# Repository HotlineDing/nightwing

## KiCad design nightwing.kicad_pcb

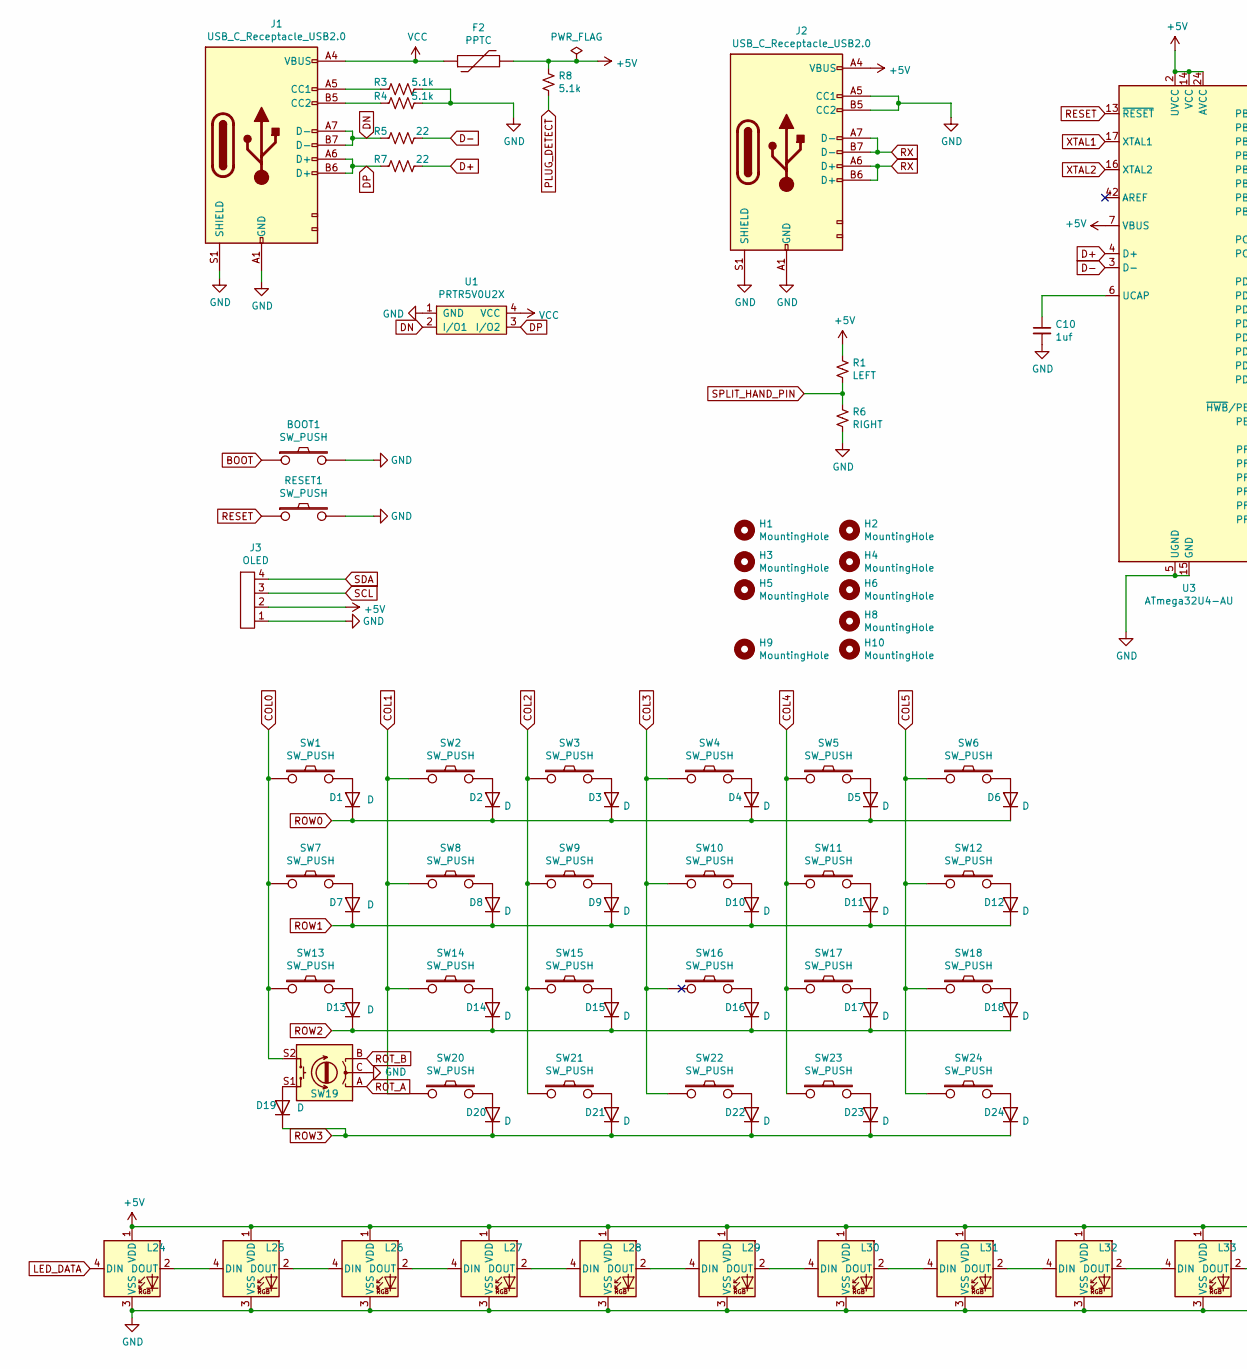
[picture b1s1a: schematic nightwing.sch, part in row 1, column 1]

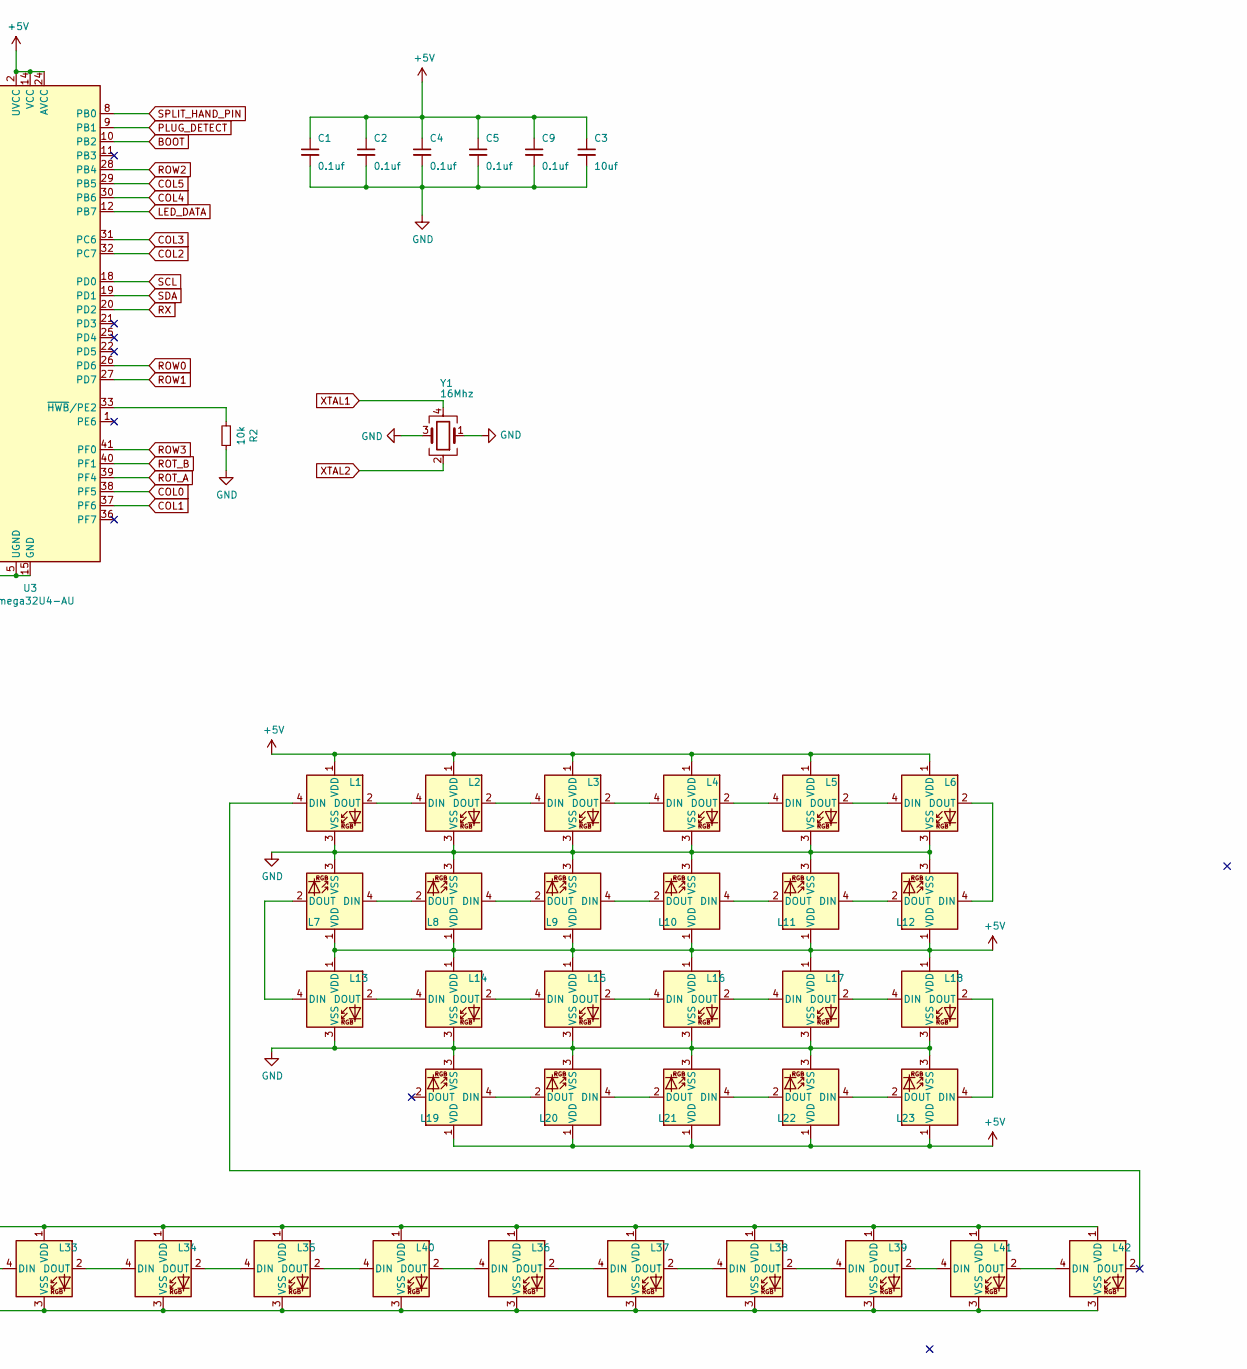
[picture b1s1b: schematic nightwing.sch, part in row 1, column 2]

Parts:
BOOT1: SW_PUSH; SW_Push_1P1T_NO_6x6mm_H9.5mm
C1, C2, C4, C5, C9: 0.1uf; C_0805_2012Metric
C3: 10uf; C_0805_2012Metric
C10: 1uf; C_0805_2012Metric
D1, D2, D3, D4, D5, D6, D7, D8, D9, D10, D11, D12, D13, D14, D15, D16, D17, D18, D19, D20, D21, D22, D23, D24: D; D_SOD-123
F2: PPTC; Fuse_1206_3216Metric
H1, H2, H3, H4, H5, H6, H8, H9, H10: MountingHole; MountingHole_2.2mm_M2_DIN965
J1, J2: USB_C_Receptacle_USB2.0; USB_C_Receptacle_HRO_TYPE-C-31-M-12
J3: OLED; OLED-SSD1306-128x64
L1, L2, L3, L4, L5, L6, L7, L8, L9, L10, L11, L12, L13, L14, L15, L16, L17, L18, L19, L20, L21, L22, L23: SK2812Mini-E; SK6812Mini-E
L24, L25, L26, L27, L28, L29, L30, L31, L32, L33, L34, L35, L36, L37, L38, L39, L40, L41, L42: WS2812B; ws2812_reversible
R1: LEFT; R_0805_2012Metric
R2: 10k; R_0805_2012Metric
R3, R4, R8: 5.1k; R_0805_2012Metric
R5, R7: 22; R_0805_2012Metric
R6: RIGHT; R_0805_2012Metric
RESET1: SW_PUSH; SW_Push_1P1T_NO_6x6mm_H9.5mm
SW1, SW2, SW3, SW4, SW5, SW6, SW7, SW8, SW9, SW10, SW11, SW12, SW13, SW14, SW15, SW16, SW17, SW18, SW20, SW21, SW22, SW23, SW24: SW_PUSH; MX-1U-Hotswap
SW19: Rotary_Encoder; RotaryEncoder_EC11
U1: PRTR5V0U2X; SOT-143_Handsoldering
U3: ATmega32U4-AU; TQFP-44_10x10mm_P0.8mm
Y1: 16Mhz; Crystal_SMD_3225-4Pin_3.2x2.5mm

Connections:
+5V: C1.1, C2.1, C3.1, C4.1, C5.1, C9.1, F2.2, J2.A4 (VBUS), J2.B4 (VBUS), J3.2, L1.1 (VDD), L2.1 (VDD), L3.1 (VDD), L4.1 (VDD), L5.1 (VDD), L6.1 (VDD), L7.1 (VDD), L8.1 (VDD), L9.1 (VDD), L10.1 (VDD), L11.1 (VDD), L12.1 (VDD), L13.1 (VDD), L14.1 (VDD), L15.1 (VDD), L16.1 (VDD), L17.1 (VDD), L18.1 (VDD), L19.1 (VDD), L20.1 (VDD), L21.1 (VDD), L22.1 (VDD), L23.1 (VDD), L24.1 (VDD), L25.1 (VDD), L26.1 (VDD), L27.1 (VDD), L28.1 (VDD), L29.1 (VDD), L30.1 (VDD), L31.1 (VDD), L32.1 (VDD), L33.1 (VDD), L34.1 (VDD), L35.1 (VDD), L36.1 (VDD), L37.1 (VDD), L38.1 (VDD), L39.1 (VDD), L40.1 (VDD), L41.1 (VDD), L42.1 (VDD), R1.1, R8.1, U3.2 (UVCC), U3.7 (VBUS), U3.14 (VCC), U3.24 (AVCC), U3.34 (VCC), U3.44 (AVCC)
BOOT: BOOT1.1, U3.10 (PB2)
COL0: SW1.1, SW7.1, SW13.1, SW19.S2, U3.38 (PF5)
COL1: SW2.1, SW8.1, SW14.1, SW20.1, U3.37 (PF6)
COL2: SW3.1, SW9.1, SW15.1, SW21.1, U3.32 (PC7)
COL3: SW4.1, SW10.1, SW16.1, SW22.1, U3.31 (PC6)
COL4: SW5.1, SW11.1, SW17.1, SW23.1, U3.30 (PB6)
COL5: SW6.1, SW12.1, SW18.1, SW24.1, U3.29 (PB5)
D+: R7.1, U3.4 (D+)
D-: R5.1, U3.3 (D-)
DN: J1.A7 (D-), J1.B7 (D-), R5.2, U1.2 (I/O1)
DP: J1.A6 (D+), J1.B6 (D+), R7.2, U1.3 (I/O2)
GND: BOOT1.2, C1.2, C2.2, C3.2, C4.2, C5.2, C9.2, C10.2, J1.A1 (GND), J1.B1 (GND), J1.S1 (SHIELD), J2.A1 (GND), J2.A5 (CC1), J2.B1 (GND), J2.B5 (CC2), J2.S1 (SHIELD), J3.1, L1.3 (VSS), L2.3 (VSS), L3.3 (VSS), L4.3 (VSS), L5.3 (VSS), L6.3 (VSS), L7.3 (VSS), L8.3 (VSS), L9.3 (VSS), L10.3 (VSS), L11.3 (VSS), L12.3 (VSS), L13.3 (VSS), L14.3 (VSS), L15.3 (VSS), L16.3 (VSS), L17.3 (VSS), L18.3 (VSS), L19.3 (VSS), L20.3 (VSS), L21.3 (VSS), L22.3 (VSS), L23.3 (VSS), L24.3 (VSS), L25.3 (VSS), L26.3 (VSS), L27.3 (VSS), L28.3 (VSS), L29.3 (VSS), L30.3 (VSS), L31.3 (VSS), L32.3 (VSS), L33.3 (VSS), L34.3 (VSS), L35.3 (VSS), L36.3 (VSS), L37.3 (VSS), L38.3 (VSS), L39.3 (VSS), L40.3 (VSS), L41.3 (VSS), L42.3 (VSS), R2.1, R3.1, R4.1, R6.2, RESET1.2, SW19.C, U1.1 (GND), U3.5 (UGND), U3.15 (GND), U3.23 (GND), U3.35 (GND), U3.43 (GND), Y1.1, Y1.3
LED_DATA: L24.4 (DIN), U3.12 (PB7)
unnamed: C10.1, U3.6 (UCAP)
unnamed: D1.2 (A), SW1.2
unnamed: D2.2 (A), SW2.2
unnamed: D3.2 (A), SW3.2
unnamed: D4.2 (A), SW4.2
unnamed: D5.2 (A), SW5.2
unnamed: D6.2 (A), SW6.2
unnamed: D7.2 (A), SW7.2
unnamed: D8.2 (A), SW8.2
unnamed: D9.2 (A), SW9.2
unnamed: D10.2 (A), SW10.2
unnamed: D11.2 (A), SW11.2
unnamed: D12.2 (A), SW12.2
unnamed: D13.2 (A), SW13.2
unnamed: D14.2 (A), SW14.2
unnamed: D15.2 (A), SW15.2
unnamed: D16.2 (A), SW16.2
unnamed: D17.2 (A), SW17.2
unnamed: D18.2 (A), SW18.2
unnamed: D19.2 (A), SW19.S1
unnamed: D20.2 (A), SW20.2
unnamed: D21.2 (A), SW21.2
unnamed: D22.2 (A), SW22.2
unnamed: D23.2 (A), SW23.2
unnamed: D24.2 (A), SW24.2
unnamed: J1.A5 (CC1), R3.2
unnamed: J1.B5 (CC2), R4.2
unnamed: L1.2 (DOUT), L2.4 (DIN)
unnamed: L1.4 (DIN), L42.2 (DOUT)
unnamed: L2.2 (DOUT), L3.4 (DIN)
unnamed: L3.2 (DOUT), L4.4 (DIN)
unnamed: L4.2 (DOUT), L5.4 (DIN)
unnamed: L5.2 (DOUT), L6.4 (DIN)
unnamed: L7.4 (DIN), L8.2 (DOUT)
unnamed: L8.4 (DIN), L9.2 (DOUT)
unnamed: L9.4 (DIN), L10.2 (DOUT)
unnamed: L10.4 (DIN), L11.2 (DOUT)
unnamed: L11.4 (DIN), L12.2 (DOUT)
unnamed: L6.2 (DOUT), L12.4 (DIN)
unnamed: L13.2 (DOUT), L14.4 (DIN)
unnamed: L7.2 (DOUT), L13.4 (DIN)
unnamed: L14.2 (DOUT), L15.4 (DIN)
unnamed: L15.2 (DOUT), L16.4 (DIN)
unnamed: L16.2 (DOUT), L17.4 (DIN)
unnamed: L17.2 (DOUT), L18.4 (DIN)
unnamed: L18.2 (DOUT), L23.4 (DIN)
unnamed: L19.4 (DIN), L20.2 (DOUT)
unnamed: L20.4 (DIN), L21.2 (DOUT)
unnamed: L21.4 (DIN), L22.2 (DOUT)
unnamed: L22.4 (DIN), L23.2 (DOUT)
unnamed: L24.2 (DOUT), L25.4 (DIN)
unnamed: L25.2 (DOUT), L26.4 (DIN)
unnamed: L26.2 (DOUT), L27.4 (DIN)
unnamed: L27.2 (DOUT), L28.4 (DIN)
unnamed: L28.2 (DOUT), L29.4 (DIN)
unnamed: L29.2 (DOUT), L30.4 (DIN)
unnamed: L30.2 (DOUT), L31.4 (DIN)
unnamed: L31.2 (DOUT), L32.4 (DIN)
unnamed: L32.2 (DOUT), L33.4 (DIN)
unnamed: L33.2 (DOUT), L34.4 (DIN)
unnamed: L34.2 (DOUT), L35.4 (DIN)
unnamed: L35.2 (DOUT), L40.4 (DIN)
unnamed: L36.2 (DOUT), L37.4 (DIN)
unnamed: L36.4 (DIN), L40.2 (DOUT)
unnamed: L37.2 (DOUT), L38.4 (DIN)
unnamed: L38.2 (DOUT), L39.4 (DIN)
unnamed: L39.2 (DOUT), L41.4 (DIN)
unnamed: L41.2 (DOUT), L42.4 (DIN)
unnamed: R2.2, U3.33 (~HWB~/PE2)
PLUG_DETECT: R8.2, U3.9 (PB1)
RESET: RESET1.1, U3.13 (~RESET)
ROT_A: SW19.A, U3.39 (PF4)
ROT_B: SW19.B, U3.40 (PF1)
ROW0: D1.1 (K), D2.1 (K), D3.1 (K), D4.1 (K), D5.1 (K), D6.1 (K), U3.26 (PD6)
ROW1: D7.1 (K), D8.1 (K), D9.1 (K), D10.1 (K), D11.1 (K), D12.1 (K), U3.27 (PD7)
ROW2: D13.1 (K), D14.1 (K), D15.1 (K), D16.1 (K), D17.1 (K), D18.1 (K), U3.28 (PB4)
ROW3: D19.1 (K), D20.1 (K), D21.1 (K), D22.1 (K), D23.1 (K), D24.1 (K), U3.41 (PF0)
RX: J2.A6 (D+), J2.A7 (D-), J2.B6 (D+), J2.B7 (D-), U3.20 (PD2)
SCL: J3.3, U3.18 (PD0)
SDA: J3.4, U3.19 (PD1)
SPLIT_HAND_PIN: R1.2, R6.1, U3.8 (PB0)
VCC: F2.1, J1.A4 (VBUS), J1.B4 (VBUS), U1.4 (VCC)
XTAL1: U3.17 (XTAL1), Y1.4
XTAL2: U3.16 (XTAL2), Y1.2

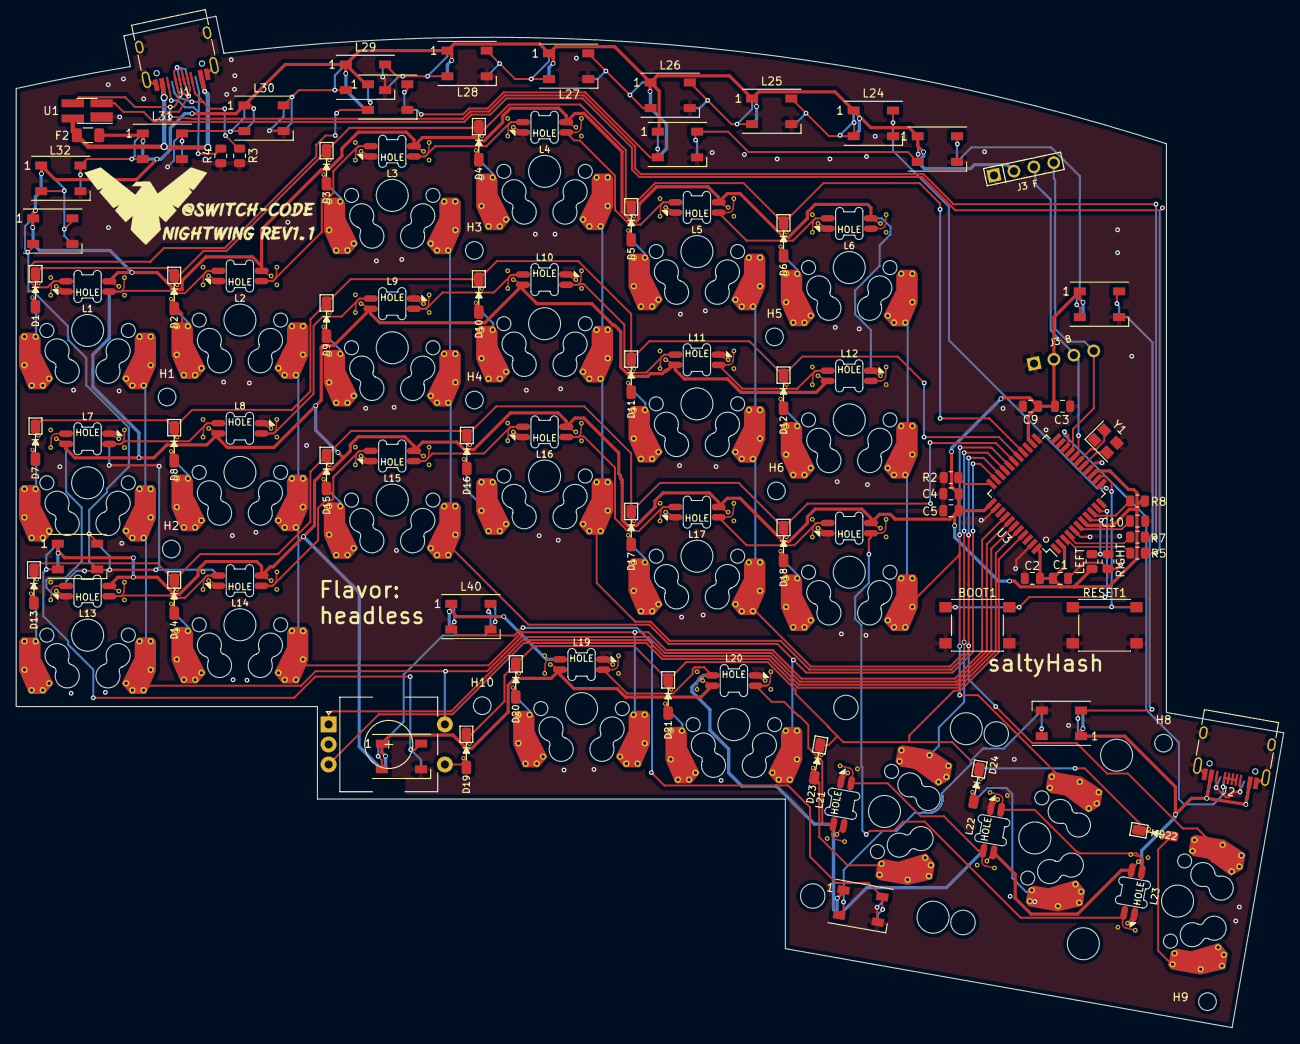
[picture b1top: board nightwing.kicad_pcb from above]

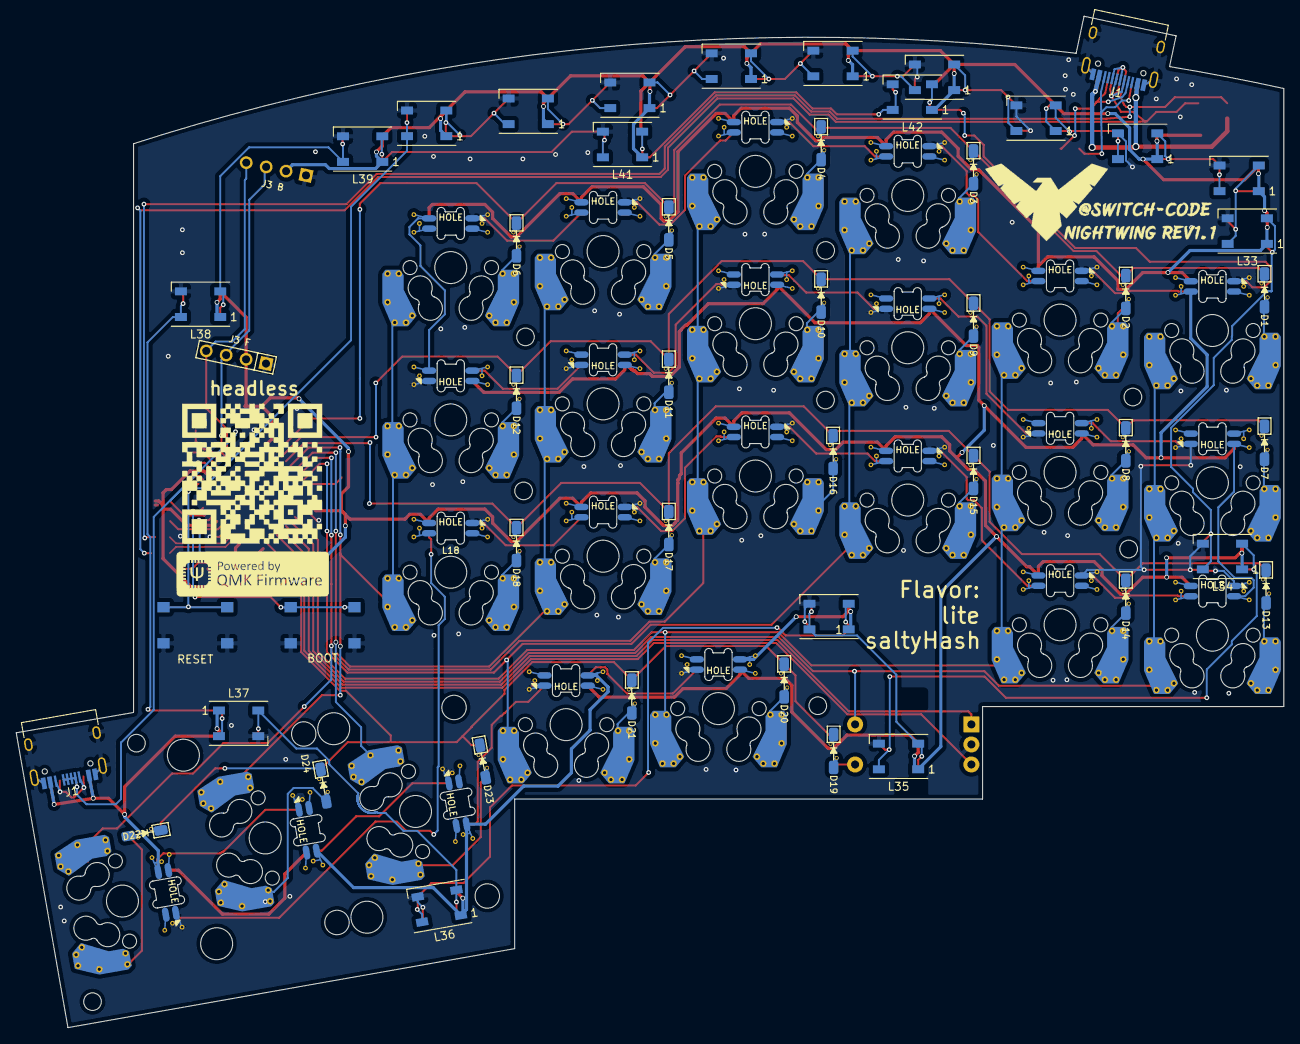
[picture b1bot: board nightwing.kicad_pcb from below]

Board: 2 copper layers, 158.1 x 126.1 mm, 133 parts (13 on the bottom side), 98 nets.

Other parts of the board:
Kailh PG1350: Choc; Kailh-PG1350-1.5u
Ref**: Val**; drawing-rev1
Ref**#2, Ref**#3: Val**; name-icon
Ref**#4: Val**; drawing-rev1
Ref**#5: Val**; rev1.1
Ref**#6: Val**; qmk_logo
Ref**#7: Val**; nightwing_qmk
SW_2u-E6, SW_2u-E6#2: MX; Triple-Dual-2u-LED

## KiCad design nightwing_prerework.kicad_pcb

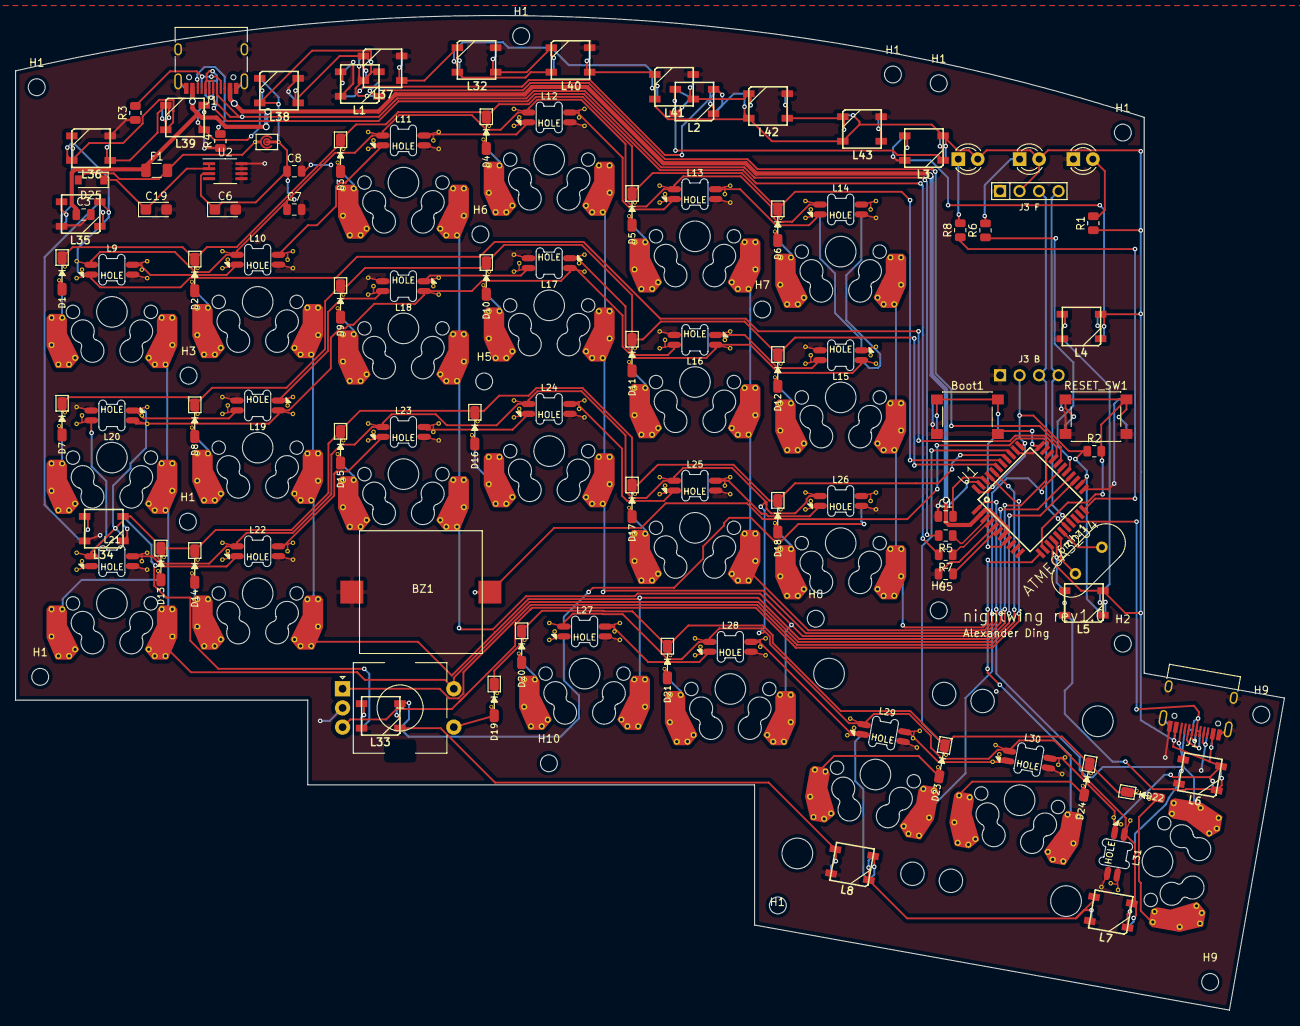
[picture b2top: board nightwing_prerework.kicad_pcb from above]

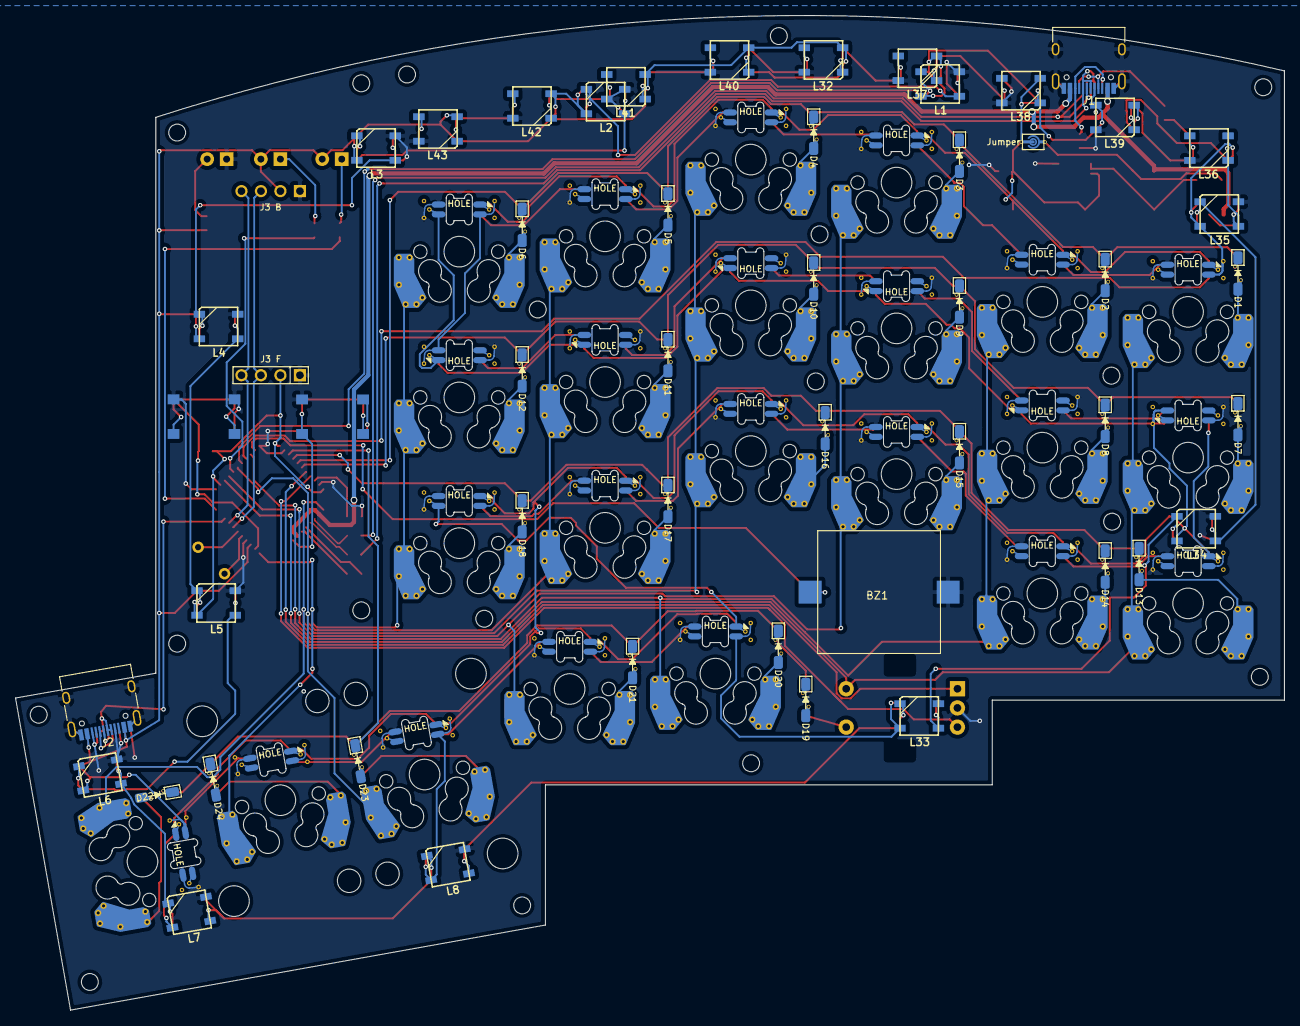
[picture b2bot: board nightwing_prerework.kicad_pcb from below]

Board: 2 copper layers, 165.4 x 129.6 mm, 140 parts (35 on the bottom side), 101 nets.

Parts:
16mhz1: Crystal; Crystal_HC49-4H_Vertical
BZ1: Buzzer
Boot1: SW_PUSH; SW_Push_1P1T_NO_6x6mm_H9.5mm
C1: 0.1uF; C_0805_2012Metric
C3, C5, C7, C8: 1uF; C_0805_2012Metric
C6, C19: 10uF; CP_EIA-3216-10_Kemet-I
D1, D2, D3, D4, D5, D6, D7, D8, D9, D10, D11, D12, D13, D14, D15, D16, D17, D18, D19, D20, D21, D22, D23, D24, D25: D; D_SOD-123
D26: Green; LED_D3.0mm
D27: Yellow; LED_D3.0mm
F1: PPTC; Fuse_1206_3216Metric
H1, H1#2, H1#3, H1#4, H1#5, H1#6, H1#7, H1#8, H2, H3, H4, H5, H6, H7, H8, H9, H9#2, H10: Hole; MountingHole_2.2mm_M2
J1, J2: USB_C_Receptacle_USB2.0; USB_C_Receptacle_HRO_TYPE-C-31-M-12
J3: OLED; OLED-SSD1306-128x64
JP1: Jumper; SolderJumper-1.0x1.5mm
Kailh PG1350: Choc; Kailh-PG1350-1.5u
L1, L2, L3, L4, L5, L6, L7, L8, L32, L33, L34, L35, L36, L37, L38, L39, L40, L41, L42, L43: WS2812_LED; WS2812B_LED
L9, L10, L11, L12, L13, L14, L15, L16, L17, L18, L19, L20, L21, L22, L23, L24, L25, L26, L27, L28, L29, L30, L31: SK6812_mini; SK6812Mini-E
R1: 1K; R_0805_2012Metric
R2: 10k; R_0805_2012Metric
R3, R4: 5.1k; R_0805_2012Metric
R5, R7: 22; R_0805_2012Metric
R6, R8: 330; R_0805_2012Metric
RED1: LED1; LED_D3.0mm
RESET_SW1: SW_PUSH; SW_Push_1P1T_NO_6x6mm_H9.5mm
SW1, SW2, SW3, SW4, SW5, SW6, SW7, SW8, SW9, SW10, SW11, SW12, SW13, SW14, SW15, SW16, SW17, SW18, SW20, SW21, SW22, SW23, SW24: SW_PUSH; MX-1U-Hotswap
SW19: Rotary_Encoder; RotaryEncoder_EC11
U1: ATMEGA32U4; ATMEGA32U4-AU
U2: MIC5219-5.0YMM; MSOP-8_3x3mm_P0.65mm

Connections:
COL0: SW1.1, SW7.1, SW13.1, SW19.S2, U1.25
COL1: SW2.1, SW8.1, SW14.1, SW20.1, U1.31
COL2: SW3.1, SW9.1, SW15.1, SW21.1, U1.26
COL3: SW4.1, SW10.1, SW16.1, SW22.1, U1.1
COL4: SW5.1, SW11.1, SW17.1, SW23.1, U1.28
COL5: SW6.1, SW12.1, SW18.1, SW24.1, U1.12
D9: L1.3, U1.29
D10: L9.3, U1.30
D+: R7.1, U1.4
D-: R5.1, U1.3
GND: BZ1.2, Boot1.2, C1.1, C3.2, C5.2, C6.2, C7.2, C8.2, C19.2, J1.A1, J1.B1, J1.S1, J2.A1, J2.A5, J2.B1, J2.B5, J2.S1, J3.1, L1.2, L2.2, L3.2, L4.2, L5.2, L6.2, L7.2, L8.2, L9.2, L10.2, L11.2, L12.2, L13.2, L14.2, L15.2, L16.2, L17.2, L18.2, L19.2, L20.2, L21.2, L22.2, L23.2, L24.2, L25.2, L26.2, L27.2, L28.2, L29.2, L30.2, L31.2, L32.2, L33.2, L34.2, L35.2, L36.2, L37.2, L38.2, L39.2, L40.2, L41.2, L42.2, L43.2, RED1.1, RESET_SW1.2, SW19.C, U1.5, U1.15, U1.23, U1.33, U1.35, U1.43, U2.5, U2.6, U2.7, U2.8
unnamed: 16mhz1.1, U1.16
unnamed: 16mhz1.2, U1.17
unnamed: Boot1.1, U1.8
unnamed: C1.2, U1.42
unnamed: C5.1, U1.6
unnamed: D1.2, SW1.2
unnamed: D2.2, SW2.2
unnamed: D3.2, SW3.2
unnamed: D4.2, SW4.2
unnamed: D5.2, SW5.2
unnamed: D6.2, SW6.2
unnamed: D7.2, SW7.2
unnamed: D8.2, SW8.2
unnamed: D9.2, SW9.2
unnamed: D10.2, SW10.2
unnamed: D11.2, SW11.2
unnamed: D12.2, SW12.2
unnamed: D13.2, SW13.2
unnamed: D14.2, SW14.2
unnamed: D15.2, SW15.2
unnamed: D16.2, SW16.2
unnamed: D17.2, SW17.2
unnamed: D18.2, SW18.2
unnamed: D19.2, SW19.S1
unnamed: D20.2, SW20.2
unnamed: D21.2, SW21.2
unnamed: D22.2, SW22.2
unnamed: D23.2, SW23.2
unnamed: D24.2, SW24.2
unnamed: D25.2, F1.2, JP1.1
unnamed: D26.1, R8.2
unnamed: D27.1, R6.2
unnamed: J1.A5, R3.2
unnamed: J1.A6, J1.B6, R7.2
unnamed: J1.A7, J1.B7, R5.2
unnamed: J1.B5, R4.2
unnamed: L1.1, L2.3
unnamed: L2.1, L3.3
unnamed: L3.1, L4.3
unnamed: L4.1, L5.3
unnamed: L5.1, L6.3
unnamed: L6.1, L7.3
unnamed: L7.1, L8.3
unnamed: L10.1, L11.3
unnamed: L9.1, L10.3
unnamed: L11.1, L12.3
unnamed: L12.1, L13.3
unnamed: L13.1, L14.3
unnamed: L14.1, L15.3
unnamed: L15.1, L16.3
unnamed: L16.1, L17.3
unnamed: L17.1, L18.3
unnamed: L18.1, L19.3
unnamed: L19.1, L20.3
unnamed: L20.1, L21.3
unnamed: L21.1, L22.3
unnamed: L22.1, L23.3
unnamed: L23.1, L24.3
unnamed: L24.1, L25.3
unnamed: L25.1, L26.3
unnamed: L26.1, L27.3
unnamed: L27.1, L28.3
unnamed: L28.1, L29.3
unnamed: L29.1, L30.3
unnamed: L30.1, L31.3
unnamed: L32.1, L40.3
unnamed: L32.3, L37.1
unnamed: L33.1, L34.3
unnamed: L8.1, L33.3
unnamed: L34.1, L35.3
unnamed: L35.1, L36.3
unnamed: L36.1, L39.3
unnamed: L37.3, L38.1
unnamed: L38.3, L39.1
unnamed: L40.1, L41.3
unnamed: L41.1, L42.3
unnamed: L42.1, L43.3
unnamed: R1.2, RED1.2
unnamed: R3.1, R4.1
unnamed: R6.1, U1.27
unnamed: R8.1, U1.22
RAW: C19.1, D25.1, U2.1, U2.2
RESET: R2.2, RESET_SW1.1, U1.13
ROW0: D1.1, D2.1, D3.1, D4.1, D5.1, D6.1
ROW1: D7.1, D8.1, D9.1, D10.1, D11.1, D12.1
ROW2: D13.1, D14.1, D15.1, D16.1, D17.1, D18.1
ROW3: D19.1, D20.1, D21.1, D22.1, D23.1, D24.1
RX: J2.A6, J2.B7, U1.20
UVCC: C3.1, F1.1, U1.2, U1.7
VCC: C6.1, C7.1, C8.1, D26.2, D27.2, J1.A4, J1.B4, J2.A4, J2.B4, J3.2, JP1.2, L1.4, L2.4, L3.4, L4.4, L5.4, L6.4, L7.4, L8.4, L9.4, L10.4, L11.4, L12.4, L13.4, L14.4, L15.4, L16.4, L17.4, L18.4, L19.4, L20.4, L21.4, L22.4, L23.4, L24.4, L25.4, L26.4, L27.4, L28.4, L29.4, L30.4, L31.4, L32.4, L33.4, L34.4, L35.4, L36.4, L37.4, L38.4, L39.4, L40.4, L41.4, L42.4, L43.4, R1.1, R2.1, U1.14, U1.24, U1.34, U1.44, U2.3

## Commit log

2021-05-10 nightwing
2021-05-11 nightwing pre nick
2021-05-11 fixed drc check
2021-05-14 fixed dangling trace a5
2021-05-14 update gerbers
2021-05-17 final pub
2021-05-17 stm_nightwing
2021-05-23 stm_nightwing finished
2021-05-24 updated stm32
2021-05-25 updated final verseion
2021-05-26 final output jlcpcb
2021-05-31 post fabrication
2021-06-11 fixed missing capactior
2021-06-19 inital rev1.1
